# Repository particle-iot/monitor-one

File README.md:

# monitor-one

*Hardware design files for the Particle Monitor One*

- [Datasheet](https://docs.particle.io/reference/datasheets/tracker/monitor-one-datasheet/)

- Design files for Eagle CAD for expansion cards can be found in the expansion-cards directory.

- CAD files for the mounting plate can be found in the cad directory.

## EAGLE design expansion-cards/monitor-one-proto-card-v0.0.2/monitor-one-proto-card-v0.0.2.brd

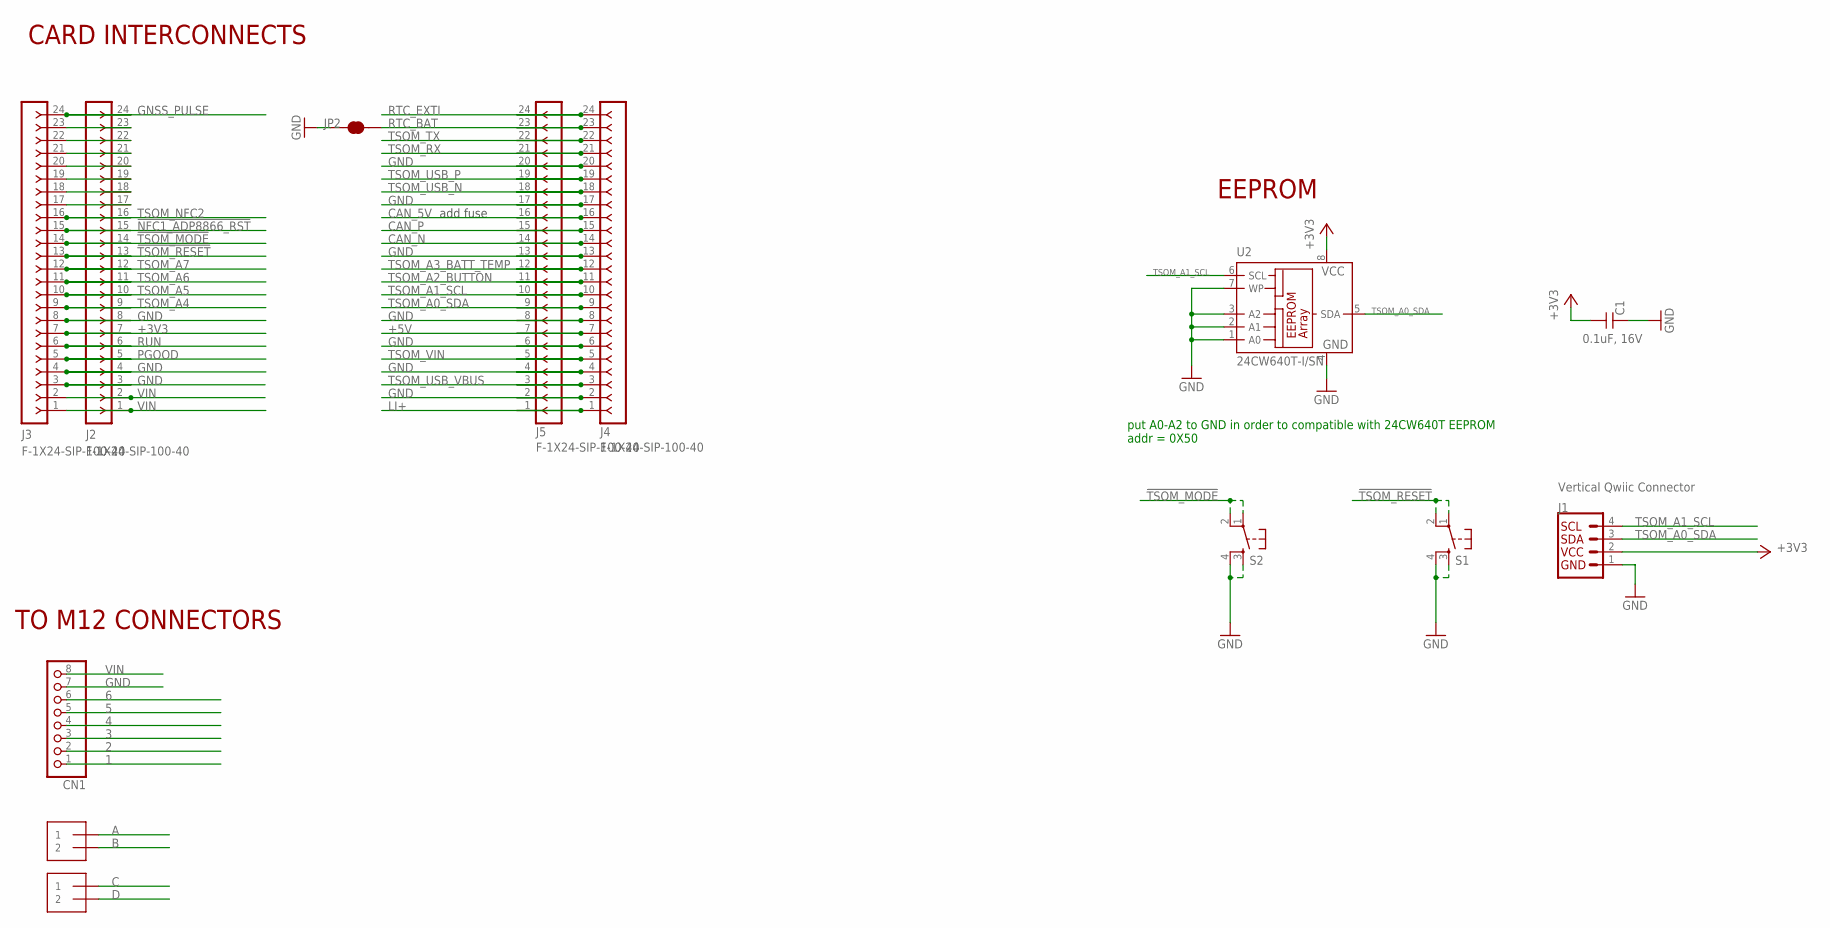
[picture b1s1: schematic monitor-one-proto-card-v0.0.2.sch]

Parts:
C1: 0.1uF, 16V; C0603_P
CN1: JST_8PIN; JSTPH8
J1: Vertical Qwiic Connector; JST04_1MM_VERT
J2, J3, J4, J5: F-1X24-SIP-100-40; SIP-100-24-40
J8, J9: 1X2-3.5MM
JP2: JUMPER-SMT_2_NC_TRACE_NO-SILK; SMT-JUMPER_2_NC_TRACE_NO-SILK
S1, S2: TAC_SWITCHSMD; TACTILE_SWITCH_SMD
U2: 24CW640T-I/SN; SO-08

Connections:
1: CN1.1
2: CN1.2
3: CN1.3
4: CN1.4
5: CN1.5
6: CN1.6
!NFC1_ADP8866_RST: J2.15, J3.15
!TSOM_MODE: J2.14, J3.14, S2.1, S2.2
!TSOM_RESET: J2.13, J3.13, S1.1, S1.2
+3V3: C1.1, J1.2, J2.7, J3.7, U2.8 (VCC)
+5V: J4.7, J5.7
A: J8.1
B: J8.2
C: J9.1
CAN_5V: J4.16, J5.16
CAN_N: J4.14, J5.14
CAN_P: J4.15, J5.15
D: J9.2
GND: C1.2, CN1.7, J1.1, J2.3, J2.4, J2.8, J3.3, J3.4, J3.8, J4.2, J4.4, J4.6, J4.8, J4.13, J4.17, J4.20, J5.2, J5.4, J5.6, J5.8, J5.13, J5.17, J5.20, JP2.1, S1.3, S1.4, S2.3, S2.4, U2.1 (A0), U2.2 (A1), U2.3 (A2), U2.4 (GND), U2.7 (WP)
GNSS_PULSE: J2.24, J3.24
LI+: J4.1, J5.1
unnamed: J2.17, J3.17
unnamed: J2.18, J3.18
unnamed: J2.19, J3.19
unnamed: J2.20, J3.20
unnamed: J2.21, J3.21
unnamed: J2.22, J3.22
unnamed: J2.23, J3.23
PGOOD: J2.5, J3.5
RTC_BAT: J4.23, J5.23, JP2.2
RTC_EXTI: J4.24, J5.24
RUN: J2.6, J3.6
TSOM_A0_SDA: J1.3, J4.9, J5.9, U2.5 (SDA)
TSOM_A1_SCL: J1.4, J4.10, J5.10, U2.6 (SCL)
TSOM_A2_BUTTON: J4.11, J5.11
TSOM_A3_BATT_TEMP: J4.12, J5.12
TSOM_A4: J2.9, J3.9
TSOM_A5: J2.10, J3.10
TSOM_A6: J2.11, J3.11
TSOM_A7: J2.12, J3.12
TSOM_NFC2: J2.16, J3.16
TSOM_RX: J4.21, J5.21
TSOM_TX: J4.22, J5.22
TSOM_USB_N: J4.18, J5.18
TSOM_USB_P: J4.19, J5.19
TSOM_USB_VBUS: J4.3, J5.3
TSOM_VIN: J4.5, J5.5
VIN: CN1.8, J2.1, J2.2, J3.1, J3.2

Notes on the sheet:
add fuse
CARD INTERCONNECTS
EEPROM
put A0-A2 to GND in order to compatible with 24CW640T EEPROM addr = 0X50
TO M12 CONNECTORS

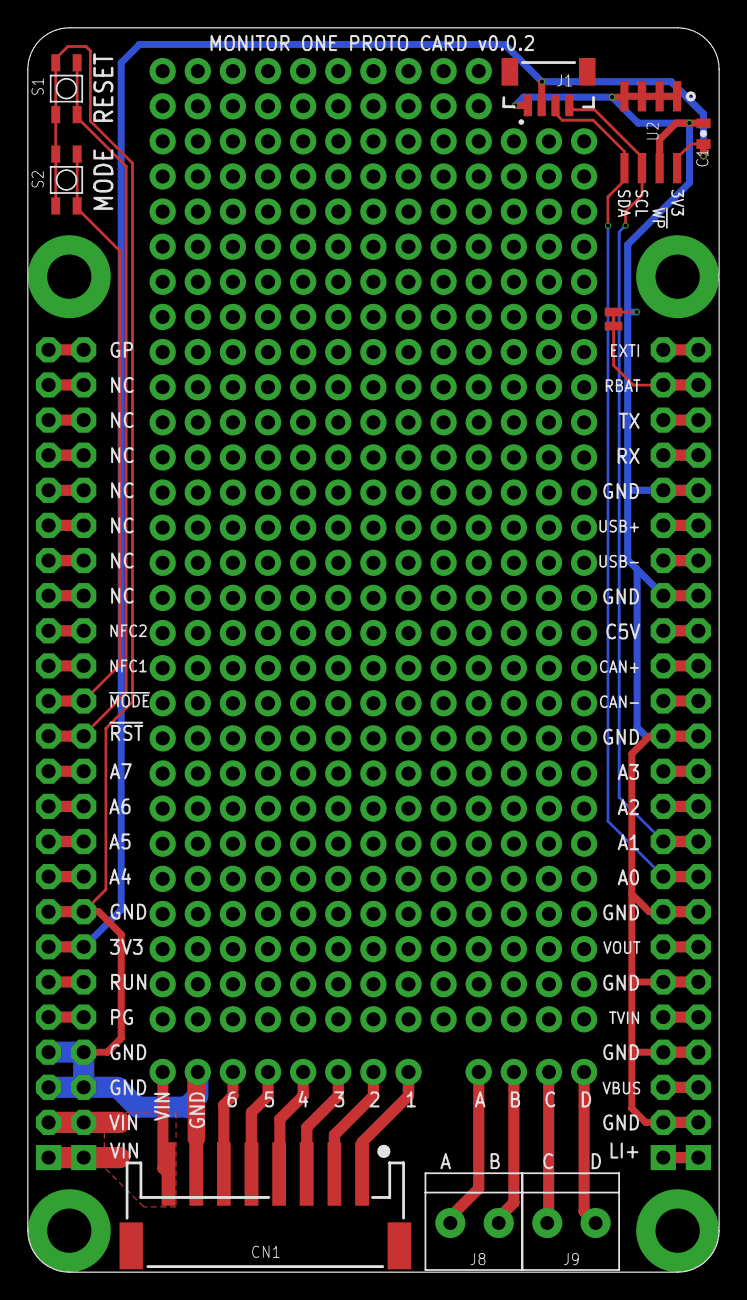
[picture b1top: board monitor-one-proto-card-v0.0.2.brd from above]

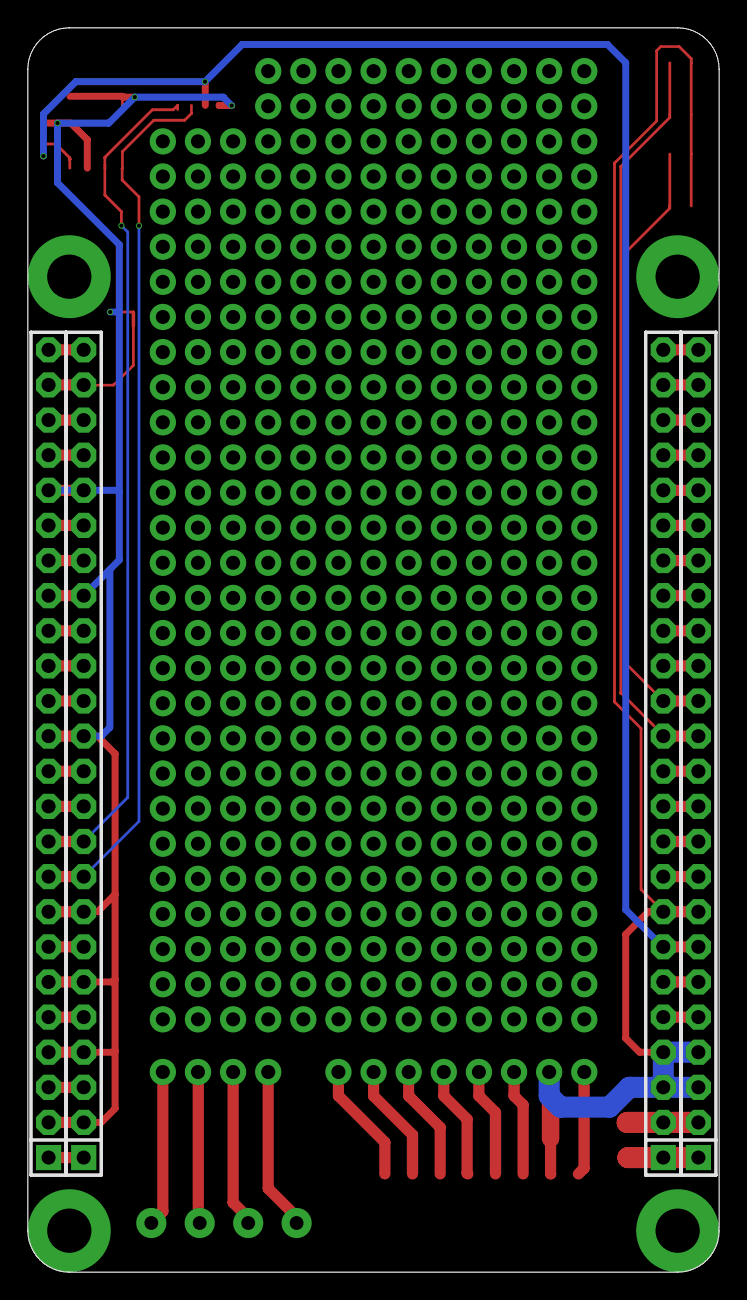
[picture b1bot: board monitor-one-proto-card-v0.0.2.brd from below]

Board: 2 copper layers, 50.0 x 90.0 mm, 13 parts (4 on the bottom side), 38 nets.

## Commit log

2023-09-08 Initial version
2026-04-22 add Gerber files

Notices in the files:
parts and their libraries:
con-headers-jp: Copyright (C) 2008, Bob Starr
microbuilder: This work is placed in the public domain, and may be freely used for commercial and non-commercial work with the following conditions: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
